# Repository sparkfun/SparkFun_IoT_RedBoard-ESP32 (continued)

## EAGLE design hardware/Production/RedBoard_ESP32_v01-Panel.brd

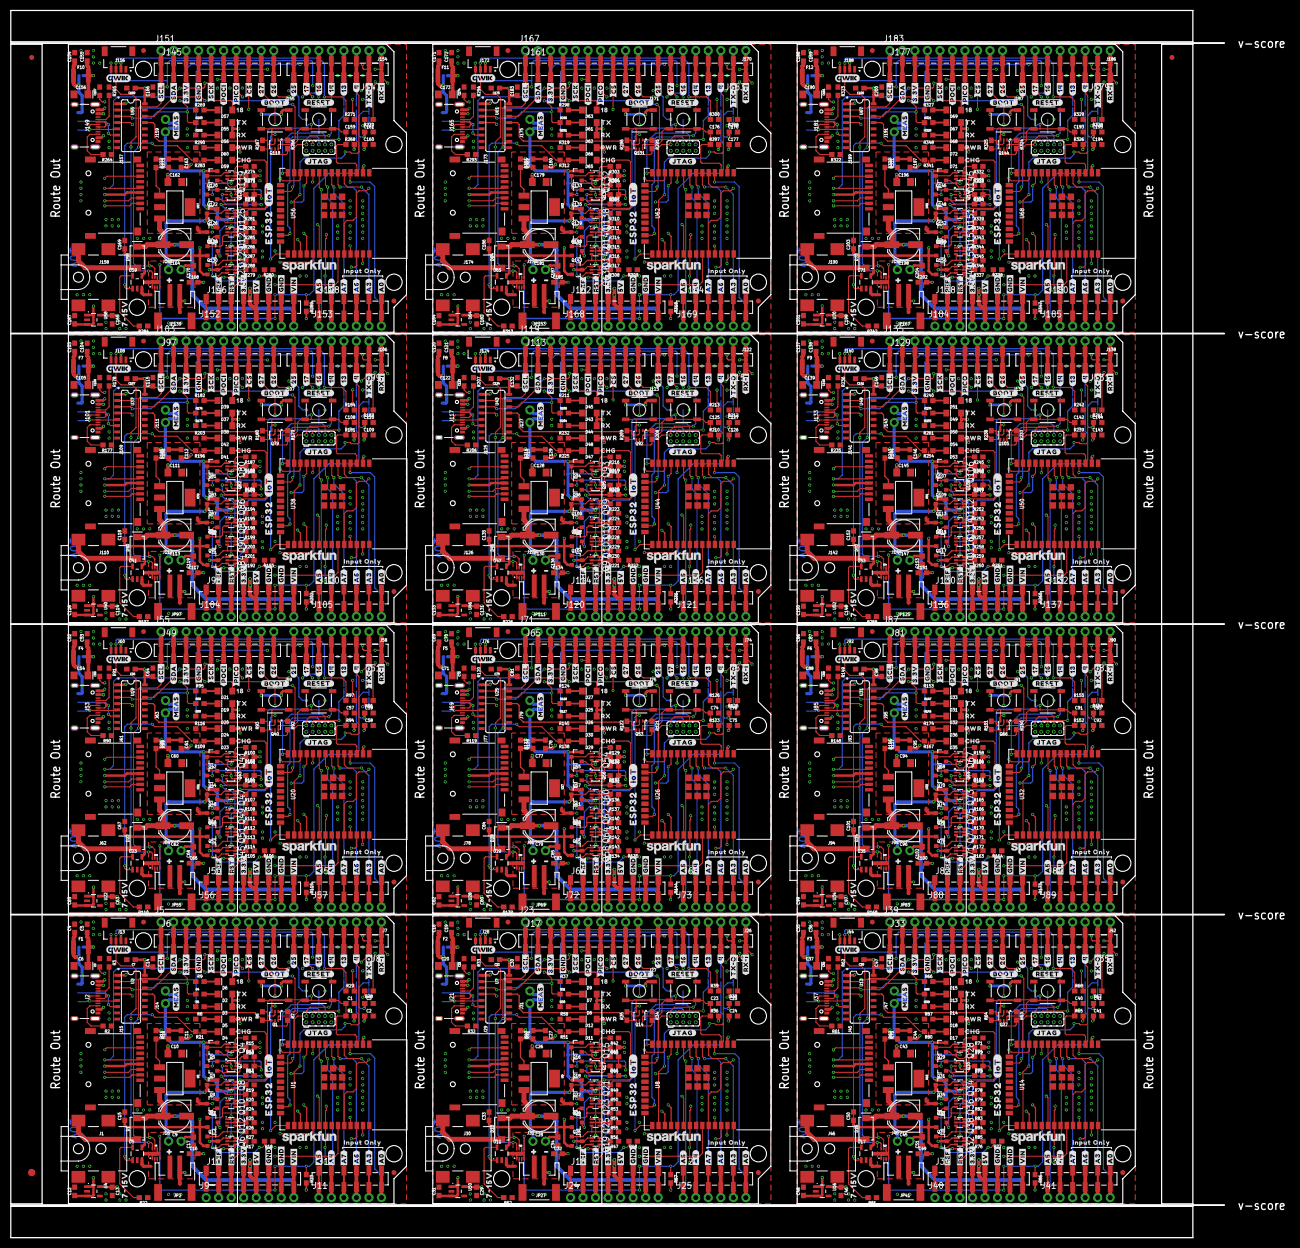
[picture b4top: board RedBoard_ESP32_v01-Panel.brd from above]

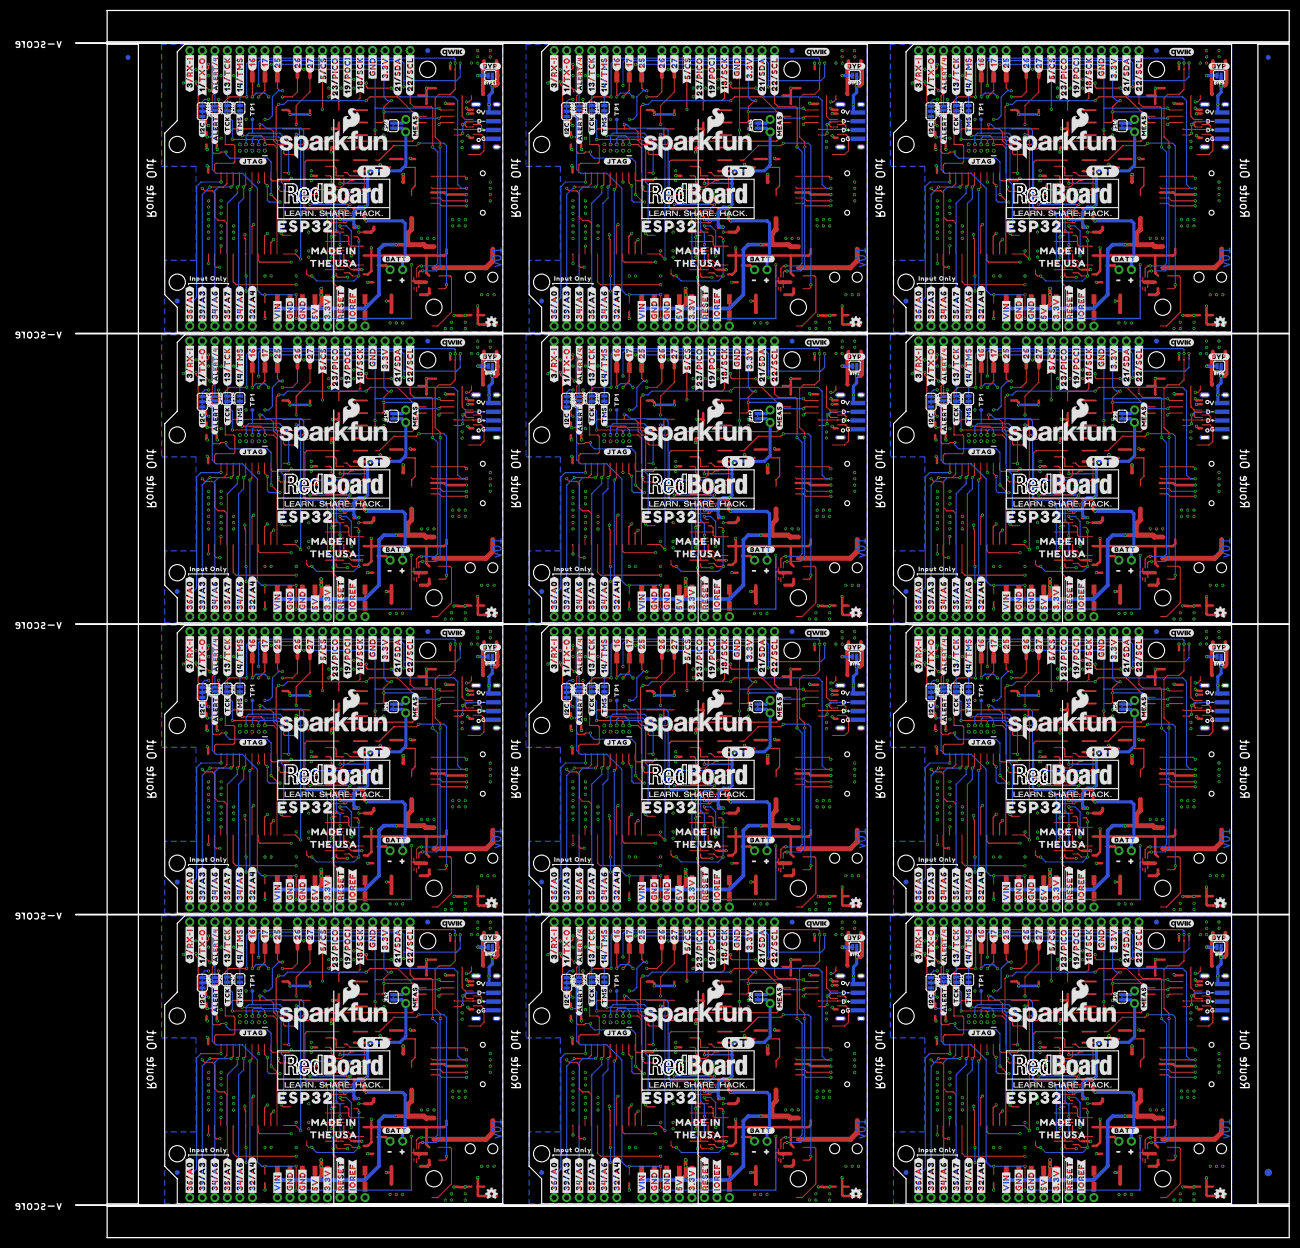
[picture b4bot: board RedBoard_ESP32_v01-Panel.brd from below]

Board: 4 copper layers, 246.1 x 248.9 mm, 2514 parts (783 on the bottom side), 876 nets.

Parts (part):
BYP, BYP1, BYP2, BYP3, BYP4, BYP5, BYP6, BYP7, BYP8, BYP9, BYP10, BYP11: JUMPER-SMT_2_NO_SILK; SMT-JUMPER_2_NO_SILK
C1, C2, C4, C5, C7, C11, C12, C13, C17, C18, C19, C22, C23, C24, C27, C29, C31, C34, C35, C36, C39, C40, C41, C44, C46, C48, C51, C52, C53, C56, C57, C58, C61, C63, C65, C68, C69, C70, C73, C74, C75, C78, C80, C82, C85, C86, C87, C90, C91, C92, C95, C97, C99, C102, C103, C104, C107, C108, C109, C112, C114, C116, C119, C120, C121, C124, C125, C126, C129, C131, C133, C136, C137, C138, C141, C142, C143, C146, C148, C150, C153, C154, C155, C158, C159, C160, C163, C165, C167, C170, C171, C172, C175, C176, C177, C180, C182, C184, C187, C188, C189, C192, C193, C194, C197, C199, C201, C204: 0.1uF; 0603
C3, C14, C25, C30, C42, C47, C59, C64, C76, C81, C93, C98, C110, C115, C127, C132, C144, C149, C161, C166, C178, C183, C195, C200: 10uF; 0603
C6, C10, C20, C26, C37, C43, C54, C60, C71, C77, C88, C94, C105, C111, C122, C128, C139, C145, C156, C162, C173, C179, C190, C196: 10uF; EIA3216
C8, C21, C38, C55, C72, C89, C106, C123, C140, C157, C174, C191: 10nF; 0603
C9, C28, C45, C62, C79, C96, C113, C130, C147, C164, C181, C198: 47uF; PANASONIC_D
C15, C16, C32, C33, C49, C50, C66, C67, C83, C84, C100, C101, C117, C118, C134, C135, C151, C152, C168, C169, C185, C186, C202, C203: 4.7uF; 0603
D1, D10, D16, D22, D28, D34, D40, D46, D52, D58, D64, D70: 1A/40V/500mV; SMA-DIODE
D2, D7, D13, D19, D25, D31, D37, D43, D49, D55, D61, D67: GREEN; LED-1206-HIDDENSILK
D3, D8, D14, D20, D26, D32, D38, D44, D50, D56, D62, D68: YELLOW; LED-1206-HIDDENSILK
D4, D11, D17, D23, D29, D35, D41, D47, D53, D59, D65, D71: RED; LED-1206-HIDDENSILK
D5, D12, D18, D24, D30, D36, D42, D48, D54, D60, D66, D72: PWR; LED-1206-HIDDENSILK
D6, D9, D15, D21, D27, D33, D39, D45, D51, D57, D63, D69: BLUE; LED-1206-HIDDENSILK
E$1, E$2, E$3, E$4: FIDUCIAL-1X2
E$5, E$6: FIDUCIAL-1.5X3
F1, F2, F3, F4, F5, F6, F7, F8, F9, F10, F11, F12: 6V/2A; 1210
J1, J30, J46, J62, J78, J94, J110, J126, J142, J158, J174, J190: 5.5x2.1mm Barrel; POWER_JACK_SMD
J2, J21, J37, J53, J69, J85, J101, J117, J133, J149, J165, J181: USB C; USB-C-16P-2LAYER-PADS
J3, J22, J38, J54, J70, J86, J102, J118, J134, J150, J166, J182: USB_SOLDER_PADS; USB-SOLDER-PADS
J4, J27, J43, J59, J75, J91, J107, J123, J139, J155, J171, J187: 2X5_PTH_SILK_.05
J5, J23, J39, J55, J71, J87, J103, J119, J135, J151, J167, J183: M10NO_SILK; 1X10_NO_SILK
J6, J17, J33, J49, J65, J81, J97, J113, J129, J145, J161, J177: 1X10_SMD_COMBINED
J7, J9, J24, J26, J40, J42, J56, J58, J72, J74, J88, J90, J104, J106, J120, J122, J136, J138, J152, J154, J168, J170, J184, J186: 1X08_NO_SILK
J8, J10, J18, J19, J34, J35, J50, J51, J66, J67, J82, J83, J98, J99, J114, J115, J130, J131, J146, J147, J162, J163, J178, J179: 1X08_SMD_COMBINED
J11, J25, J41, J57, J73, J89, J105, J121, J137, J153, J169, J185: 1X06_NO_SILK
J12, J20, J36, J52, J68, J84, J100, J116, J132, J148, J164, J180: 1X06_SMD_STRAIGHT_COMBO
J13, J28, J44, J60, J76, J92, J108, J124, J140, J156, J172, J188: QWIIC_RIGHT_ANGLE; JST04_1MM_RA
J14, J16, J31, J32, J47, J48, J63, J64, J79, J80, J95, J96, J111, J112, J127, J128, J143, J144, J159, J160, J175, J176, J191, J192: 1X02_NO_SILK
J15, J29, J45, J61, J77, J93, J109, J125, J141, J157, J173, J189: MICRO-SD-PUSH-PUSH-EXT-PIN; MICROSD-EXTERNALPIN
JP1, JP7, JP8, JP9, JP19, JP20, JP21, JP22, JP33, JP34, JP35, JP36, JP47, JP48, JP49, JP50, JP61, JP62, JP63, JP64, JP75, JP76, JP77, JP78, JP89, JP90, JP91, JP92, JP103, JP104, JP105, JP106, JP117, JP118, JP119, JP120, JP131, JP132, JP133, JP134, JP145, JP146, JP147, JP148, JP159, JP160, JP161, JP162: FIDUCIAL1X2; FIDUCIAL-1X2
JP2, JP27, JP41, JP55, JP69, JP83, JP97, JP111, JP125, JP139, JP153, JP167: LiPo; JST-2-SMD
JP3, JP4, JP5, JP6, JP15, JP16, JP17, JP18, JP29, JP30, JP31, JP32, JP43, JP44, JP45, JP46, JP57, JP58, JP59, JP60, JP71, JP72, JP73, JP74, JP85, JP86, JP87, JP88, JP99, JP100, JP101, JP102, JP113, JP114, JP115, JP116, JP127, JP128, JP129, JP130, JP141, JP142, JP143, JP144, JP155, JP156, JP157, JP158: STAND-OFF
JP10, JP13, JP14, JP25, JP26, JP28, JP39, JP40, JP42, JP53, JP54, JP56, JP67, JP68, JP70, JP81, JP82, JP84, JP95, JP96, JP98, JP109, JP110, JP112, JP123, JP124, JP126, JP137, JP138, JP140, JP151, JP152, JP154, JP165, JP166, JP168: JUMPER-SMT_2_NC_TRACE_SILK; SMT-JUMPER_2_NC_TRACE_SILK
JP11, JP23, JP37, JP51, JP65, JP79, JP93, JP107, JP121, JP135, JP149, JP163: JUMPER-SMT_3_2-NC_TRACE_SILK; SMT-JUMPER_3_2-NC_TRACE_SILK
JP12, JP24, JP38, JP52, JP66, JP80, JP94, JP108, JP122, JP136, JP150, JP164: JUMPER-SMT_2_NO_SILK; SMT-JUMPER_2_NO_SILK
LOGO1, LOGO5, LOGO11, LOGO16, LOGO21, LOGO26, LOGO31, LOGO36, LOGO41, LOGO46, LOGO51, LOGO56: SFE_LOGO_NAME.1_INCH; SFE_LOGO_NAME_.1
LOGO2, LOGO4, LOGO7, LOGO9, LOGO12, LOGO14, LOGO17, LOGO19, LOGO22, LOGO24, LOGO27, LOGO29, LOGO32, LOGO34, LOGO37, LOGO39, LOGO42, LOGO44, LOGO47, LOGO49, LOGO52, LOGO54, LOGO57, LOGO59: QWIIC_LOGO_5MM; QWIIC_5MM
LOGO3, LOGO8, LOGO13, LOGO18, LOGO23, LOGO28, LOGO33, LOGO38, LOGO43, LOGO48, LOGO53, LOGO58: OSHW-LOGOMINI; OSHW-LOGO-MINI
LOGO6, LOGO10, LOGO15, LOGO20, LOGO25, LOGO30, LOGO35, LOGO40, LOGO45, LOGO50, LOGO55, LOGO60: SFE_LOGO_NAME_FLAME.2_INCH; SFE_LOGO_NAME_FLAME_.2
Q1, Q14, Q27, Q40, Q53, Q66, Q79, Q92, Q105, Q118, Q131, Q144: MBT3904DW1T1; SC70-6
Q2, Q17, Q30, Q43, Q56, Q69, Q82, Q95, Q108, Q121, Q134, Q147: SC70-6
Q3, Q5, Q7, Q9, Q11, Q13, Q16, Q18, Q20, Q22, Q24, Q26, Q29, Q31, Q33, Q35, Q37, Q39, Q42, Q44, Q46, Q48, Q50, Q52, Q55, Q57, Q59, Q61, Q63, Q65, Q68, Q70, Q72, Q74, Q76, Q78, Q81, Q83, Q85, Q87, Q89, Q91, Q94, Q96, Q98, Q100, Q102, Q104, Q107, Q109, Q111, Q113, Q115, Q117, Q120, Q122, Q124, Q126, Q128, Q130, Q133, Q135, Q137, Q139, Q141, Q143, Q146, Q148, Q150, Q152, Q154, Q156: 20V/4.2A/52mΩ/1.4W; SOT23-3
Q4, Q6, Q8, Q10, Q12, Q15, Q19, Q21, Q23, Q25, Q28, Q32, Q34, Q36, Q38, Q41, Q45, Q47, Q49, Q51, Q54, Q58, Q60, Q62, Q64, Q67, Q71, Q73, Q75, Q77, Q80, Q84, Q86, Q88, Q90, Q93, Q97, Q99, Q101, Q103, Q106, Q110, Q112, Q114, Q116, Q119, Q123, Q125, Q127, Q129, Q132, Q136, Q138, Q140, Q142, Q145, Q149, Q151, Q153, Q155: SOT363_PHILIPS
R1, R6, R7, R8, R12, R13, R14, R15, R17, R19, R23, R24, R26, R34, R35, R36, R42, R44, R45, R46, R47, R49, R53, R55, R57, R58, R63, R64, R65, R71, R73, R74, R75, R76, R78, R82, R84, R86, R87, R92, R93, R94, R100, R102, R103, R104, R105, R107, R111, R113, R115, R116, R121, R122, R123, R129, R131, R132, R133, R134, R136, R140, R142, R144, R145, R150, R151, R152, R158, R160, R161, R162, R163, R165, R169, R171, R173, R174, R179, R180, R181, R187, R189, R190, R191, R192, R194, R198, R200, R202, R203, R208, R209, R210, R216, R218, R219, R220, R221, R223, R227, R229, R231, R232, R237, R238, R239, R245, R247, R248, R249, R250, R252, R256, R258, R260, R261, R266, R267, R268, R274, R276, R277, R278, R279, R281, R285, R287, R289, R290, R295, R296, R297, R303, R305, R306, R307, R308, R310, R314, R316, R318, R319, R324, R325, R326, R332, R334, R335, R336, R337, R339, R343, R345, R347, R348: 10k; 0603
R2, R3, R32, R33, R61, R62, R90, R91, R119, R120, R148, R149, R177, R178, R206, R207, R235, R236, R264, R265, R293, R294, R322, R323: 5.1k; 0603
R4, R5, R9, R30, R31, R37, R59, R60, R66, R88, R89, R95, R117, R118, R124, R146, R147, R153, R175, R176, R182, R204, R205, R211, R233, R234, R240, R262, R263, R269, R291, R292, R298, R320, R321, R327: 4.7k; 0603
R10, R41, R70, R99, R128, R157, R186, R215, R244, R273, R302, R331: 240; 0603
R11, R40, R69, R98, R127, R156, R185, R214, R243, R272, R301, R330: 715; 0603
R16, R18, R20, R25, R27, R43, R48, R50, R54, R56, R72, R77, R79, R83, R85, R101, R106, R108, R112, R114, R130, R135, R137, R141, R143, R159, R164, R166, R170, R172, R188, R193, R195, R199, R201, R217, R222, R224, R228, R230, R246, R251, R253, R257, R259, R275, R280, R282, R286, R288, R304, R309, R311, R315, R317, R333, R338, R340, R344, R346: 47k; 0603
R21, R51, R80, R109, R138, R167, R196, R225, R254, R283, R312, R341: 1k; 0603
R22, R52, R81, R110, R139, R168, R197, R226, R255, R284, R313, R342: 2.0k; 0603
R28, R29, R38, R39, R67, R68, R96, R97, R125, R126, R154, R155, R183, R184, R212, R213, R241, R242, R270, R271, R299, R300, R328, R329: 2.2k; 0603
S1, S3, S5, S7, S9, S11, S13, S15, S17, S19, S21, S23: Reset; TACTILE_SWITCH_SMD_5.2MM
S2, S4, S6, S8, S10, S12, S14, S16, S18, S20, S22, S24: GPIO0; TACTILE_SWITCH_SMD_5.2MM
TP1, TP2, TP3, TP4, TP5, TP6, TP7, TP8, TP9, TP10, TP11, TP12: TEST-POINT3; PAD.03X.03
U1, U8, U14, U20, U26, U32, U38, U44, U50, U56, U62, U68: ESP-WROOM-3232D-NARROW; ESP-WROOM-32D-NARROW
U2, U7, U13, U19, U25, U31, U37, U43, U49, U55, U61, U67: CH340C; SO016
U3, U9, U15, U21, U27, U33, U39, U45, U51, U57, U63, U69: LM1117; SOT223
U4, U10, U16, U22, U28, U34, U40, U46, U52, U58, U64, U70: 3.3V; SOT23-5
U5, U11, U17, U23, U29, U35, U41, U47, U53, U59, U65, U71: MCP73831; SOT23-5
U6, U12, U18, U24, U30, U36, U42, U48, U54, U60, U66, U72: MAX17048; DFN-8
U$1, U$87, U$197, U$295, U$393, U$491, U$589, U$687, U$785, U$883, U$981, U$1079: V323252
U$2, U$3, U$198, U$296, U$394, U$492, U$590, U$688, U$786, U$884, U$982, U$1080: #SCL#34
U$4, U$101, U$199, U$297, U$395, U$493, U$591, U$689, U$787, U$885, U$983, U$1081: #SDA#33
U$5, U$102, U$200, U$298, U$396, U$494, U$592, U$690, U$788, U$886, U$984, U$1082: #3#3V#33
U$6, U$103, U$201, U$299, U$397, U$495, U$593, U$691, U$789, U$887, U$985, U$1083: #GND#32
U$7, U$104, U$202, U$300, U$398, U$496, U$594, U$692, U$790, U$888, U$986, U$1084: #SCK#31
U$8, U$105, U$203, U$301, U$399, U$497, U$595, U$693, U$791, U$889, U$987, U$1085: #POCI#30
U$9, U$106, U$204, U$302, U$400, U$498, U$596, U$694, U$792, U$890, U$988, U$1086: #PICO#29
U$10, U$107, U$205, U$303, U$401, U$499, U$597, U$695, U$793, U$891, U$989, U$1087: 1836
U$11, U$108, U$206, U$304, U$402, U$500, U$598, U$696, U$794, U$892, U$990, U$1088: ##CS##28
U$12, U$109, U$207, U$305, U$403, U$501, U$599, U$697, U$795, U$893, U$991, U$1089: #27#27
U$13, U$110, U$208, U$306, U$404, U$502, U$600, U$698, U$796, U$894, U$992, U$1090: #26#26
U$14, U$111, U$209, U$307, U$405, U$503, U$601, U$699, U$797, U$895, U$993, U$1091: TX1838
U$15, U$112, U$210, U$308, U$406, U$504, U$602, U$700, U$798, U$896, U$994, U$1092: RX1839
U$16, U$113, U$211, U$309, U$407, U$505, U$603, U$701, U$799, U$897, U$995, U$1093: PWR1837
U$17, U$114, U$212, U$310, U$408, U$506, U$604, U$702, U$800, U$898, U$996, U$1094: CHG1840
U$18, U$115, U$213, U$311, U$409, U$507, U$605, U$703, U$801, U$899, U$997, U$1095: #25#18
U$19, U$116, U$214, U$312, U$410, U$508, U$606, U$704, U$802, U$900, U$998, U$1096: #17#17
U$20, U$117, U$215, U$313, U$411, U$509, U$607, U$705, U$803, U$901, U$999, U$1097: #16#15
U$21, U$118, U$216, U$314, U$412, U$510, U$608, U$706, U$804, U$902, U$1000, U$1098: #14#14
U$22, U$119, U$217, U$315, U$413, U$511, U$609, U$707, U$805, U$903, U$1001, U$1099: #13#5
U$23, U$120, U$218, U$316, U$414, U$512, U$610, U$708, U$806, U$904, U$1002, U$1100: #4#2
U$24, U$121, U$219, U$317, U$415, U$513, U$611, U$709, U$807, U$905, U$1003, U$1101: #TX#O#0
U$25, U$122, U$220, U$318, U$416, U$514, U$612, U$710, U$808, U$906, U$1004, U$1102: #RX#I#1
U$26, U$123, U$221, U$319, U$417, U$515, U$613, U$711, U$809, U$907, U$1005, U$1103: #RESET#1842
U$27, U$124, U$222, U$320, U$418, U$516, U$614, U$712, U$810, U$908, U$1006, U$1104: #BOOT#1841
U$28, U$46, U$125, U$143, U$223, U$241, U$321, U$339, U$419, U$437, U$517, U$535, U$615, U$633, U$713, U$731, U$811, U$829, U$909, U$927, U$1007, U$1025, U$1105, U$1123: #JTAG#1847
U$29, U$126, U$224, U$322, U$420, U$518, U$616, U$714, U$812, U$910, U$1008, U$1106: #A0#1843
U$30, U$127, U$225, U$323, U$421, U$519, U$617, U$715, U$813, U$911, U$1009, U$1107: #A3#1843
U$31, U$128, U$226, U$324, U$422, U$520, U$618, U$716, U$814, U$912, U$1010, U$1108: #A6#1843
U$32, U$129, U$227, U$325, U$423, U$521, U$619, U$717, U$815, U$913, U$1011, U$1109: #A7#1843
U$33, U$130, U$228, U$326, U$424, U$522, U$620, U$718, U$816, U$914, U$1012, U$1110: #A4#1843
U$34, U$131, U$229, U$327, U$425, U$523, U$621, U$719, U$817, U$915, U$1013, U$1111: #A5#1843
U$35, U$132, U$230, U$328, U$426, U$524, U$622, U$720, U$818, U$916, U$1014, U$1112: #VIN#1843
U$36, U$37, U$133, U$134, U$231, U$232, U$329, U$330, U$427, U$428, U$525, U$526, U$623, U$624, U$721, U$722, U$819, U$820, U$917, U$918, U$1015, U$1016, U$1113, U$1114: #GND#1844
U$38, U$135, U$233, U$331, U$429, U$527, U$625, U$723, U$821, U$919, U$1017, U$1115: #5V#1845
U$39, U$136, U$234, U$332, U$430, U$528, U$626, U$724, U$822, U$920, U$1018, U$1116: #3#3V#1845
U$40, U$137, U$235, U$333, U$431, U$529, U$627, U$725, U$823, U$921, U$1019, U$1117: ##RST##1845
U$41, U$138, U$236, U$334, U$432, U$530, U$628, U$726, U$824, U$922, U$1020, U$1118: #REF#1846
U$42, U$81, U$139, U$176, U$237, U$274, U$335, U$372, U$433, U$470, U$531, U$568, U$629, U$666, U$727, U$764, U$825, U$862, U$923, U$960, U$1021, U$1058, U$1119, U$1156: #MEAS#1851
U$43, U$86, U$140, U$181, U$238, U$279, U$336, U$377, U$434, U$475, U$532, U$573, U$630, U$671, U$728, U$769, U$826, U$867, U$924, U$965, U$1022, U$1063, U$1120, U$1161: #1849
U$44, U$88, U$141, U$182, U$239, U$280, U$337, U$378, U$435, U$476, U$533, U$574, U$631, U$672, U$729, U$770, U$827, U$868, U$925, U$966, U$1023, U$1064, U$1121, U$1162: #1850
U$45, U$142, U$240, U$338, U$436, U$534, U$632, U$730, U$828, U$926, U$1024, U$1122: #BATT#1848
U$47, U$194, U$292, U$390, U$488, U$586, U$684, U$782, U$880, U$978, U$1076, U$1174: #IOT#132321874
U$48, U$144, U$242, U$340, U$438, U$536, U$634, U$732, U$830, U$928, U$1026, U$1124: ESP321855
U$49, U$145, U$243, U$341, U$439, U$537, U$635, U$733, U$831, U$929, U$1027, U$1125: 7#15V32321861
U$50, U$146, U$244, U$342, U$440, U$538, U$636, U$734, U$832, U$930, U$1028, U$1126: #39#A3#321862
U$51, U$147, U$245, U$343, U$441, U$539, U$637, U$735, U$833, U$931, U$1029, U$1127: #36#A0#321862
U$52, U$148, U$246, U$344, U$442, U$540, U$638, U$736, U$834, U$932, U$1030, U$1128: #34#A6#32321865
U$53, U$149, U$247, U$345, U$443, U$541, U$639, U$737, U$835, U$933, U$1031, U$1129: #35#A7#321862
U$54, U$150, U$248, U$346, U$444, U$542, U$640, U$738, U$836, U$934, U$1032, U$1130: #32#A4#32321865
U$55, U$151, U$249, U$347, U$445, U$543, U$641, U$739, U$837, U$935, U$1033, U$1131: #34#A6#321862
U$56, U$152, U$250, U$348, U$446, U$544, U$642, U$740, U$838, U$936, U$1034, U$1132: #VIN#321862
U$57, U$60, U$153, U$156, U$251, U$254, U$349, U$352, U$447, U$450, U$545, U$548, U$643, U$646, U$741, U$744, U$839, U$842, U$937, U$940, U$1035, U$1038, U$1133, U$1136: #GND#321863
U$58, U$154, U$252, U$350, U$448, U$546, U$644, U$742, U$840, U$938, U$1036, U$1134: #5V#321864
U$59, U$155, U$253, U$351, U$449, U$547, U$645, U$743, U$841, U$939, U$1037, U$1135: #3#3V#321864
U$61, U$157, U$255, U$353, U$451, U$549, U$647, U$745, U$843, U$941, U$1039, U$1137: ##RESET##321864
U$62, U$158, U$256, U$354, U$452, U$550, U$648, U$746, U$844, U$942, U$1040, U$1138: #IOREF#321865
U$63, U$159, U$257, U$355, U$453, U$551, U$649, U$747, U$845, U$943, U$1041, U$1139: #3#RX#I#32321869
U$64, U$160, U$258, U$356, U$454, U$552, U$650, U$748, U$846, U$944, U$1042, U$1140: #1#TX#O#32321869
U$65, U$189, U$287, U$385, U$483, U$581, U$679, U$777, U$875, U$973, U$1071, U$1169: ##ALERT##4#321866
U$66, U$161, U$259, U$357, U$455, U$553, U$651, U$749, U$847, U$945, U$1043, U$1141: #13#TCK#32321869
U$67, U$162, U$260, U$358, U$456, U$554, U$652, U$750, U$848, U$946, U$1044, U$1142: #14#TMS#32321869
U$68, U$163, U$261, U$359, U$457, U$555, U$653, U$751, U$849, U$947, U$1045, U$1143: #16#32321869
U$69, U$164, U$262, U$360, U$458, U$556, U$654, U$752, U$850, U$948, U$1046, U$1144: #17#32321869
U$70, U$165, U$263, U$361, U$459, U$557, U$655, U$753, U$851, U$949, U$1047, U$1145: #25#32321869
U$71, U$166, U$264, U$362, U$460, U$558, U$656, U$754, U$852, U$950, U$1048, U$1146: #26#32321869
U$72, U$167, U$265, U$363, U$461, U$559, U$657, U$755, U$853, U$951, U$1049, U$1147: #5##CS##32321869
U$73, U$168, U$266, U$364, U$462, U$560, U$658, U$756, U$854, U$952, U$1050, U$1148: #23#PICO#321866
U$74, U$169, U$267, U$365, U$463, U$561, U$659, U$757, U$855, U$953, U$1051, U$1149: #19#POCI#321866
U$75, U$170, U$268, U$366, U$464, U$562, U$660, U$758, U$856, U$954, U$1052, U$1150: #18#SCK#32321869
U$76, U$171, U$269, U$367, U$465, U$563, U$661, U$759, U$857, U$955, U$1053, U$1151: #21#SDA#32321869
U$77, U$172, U$270, U$368, U$466, U$564, U$662, U$760, U$858, U$956, U$1054, U$1152: #22#SCL#32321869
U$78, U$173, U$271, U$369, U$467, U$565, U$663, U$761, U$859, U$957, U$1055, U$1153: #27#32321869
U$79, U$174, U$272, U$370, U$468, U$566, U$664, U$762, U$860, U$958, U$1056, U$1154: #GND#321866
U$80, U$175, U$273, U$371, U$469, U$567, U$665, U$763, U$861, U$959, U$1057, U$1155: #3#3V#321866
U$82, U$177, U$275, U$373, U$471, U$569, U$667, U$765, U$863, U$961, U$1059, U$1157: #BYP#35
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
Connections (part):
3.3V: C2.1, C3.1, C7.1, C13.1, C14.1, D2.A, D3.A, D5.A, J5.3, J6.3A, J6.3B, J9.2, J9.4, J10.2, J10.4, J13.2, J15.4, JP11.2, R1.2, R23.2, U1.2, U2.16, U4.5
3.3V1: C22.1, C24.1, C25.1, C29.1, C30.1, D7.A, D8.A, D12.A, J17.3A, J17.3B, J18.2, J18.4, J23.3, J24.2, J24.4, J28.2, J29.4, JP23.2, R36.2, R57.2, U7.16, U8.2, U10.5
3.3V2: C39.1, C41.1, C42.1, C46.1, C47.1, D13.A, D14.A, D18.A, J33.3A, J33.3B, J34.2, J34.4, J39.3, J40.2, J40.4, J44.2, J45.4, JP37.2, R65.2, R86.2, U13.16, U14.2, U16.5
3.3V3: C56.1, C58.1, C59.1, C63.1, C64.1, D19.A, D20.A, D24.A, J49.3A, J49.3B, J50.2, J50.4, J55.3, J56.2, J56.4, J60.2, J61.4, JP51.2, R94.2, R115.2, U19.16, U20.2, U22.5
3.3V4: C73.1, C75.1, C76.1, C80.1, C81.1, D25.A, D26.A, D30.A, J65.3A, J65.3B, J66.2, J66.4, J71.3, J72.2, J72.4, J76.2, J77.4, JP65.2, R123.2, R144.2, U25.16, U26.2, U28.5
3.3V5: C90.1, C92.1, C93.1, C97.1, C98.1, D31.A, D32.A, D36.A, J81.3A, J81.3B, J82.2, J82.4, J87.3, J88.2, J88.4, J92.2, J93.4, JP79.2, R152.2, R173.2, U31.16, U32.2, U34.5
3.3V6: C107.1, C109.1, C110.1, C114.1, C115.1, D37.A, D38.A, D42.A, J97.3A, J97.3B, J98.2, J98.4, J103.3, J104.2, J104.4, J108.2, J109.4, JP93.2, R181.2, R202.2, U37.16, U38.2, U40.5
3.3V7: C124.1, C126.1, C127.1, C131.1, C132.1, D43.A, D44.A, D48.A, J113.3A, J113.3B, J114.2, J114.4, J119.3, J120.2, J120.4, J124.2, J125.4, JP107.2, R210.2, R231.2, U43.16, U44.2, U46.5
3.3V8: C141.1, C143.1, C144.1, C148.1, C149.1, D49.A, D50.A, D54.A, J129.3A, J129.3B, J130.2, J130.4, J135.3, J136.2, J136.4, J140.2, J141.4, JP121.2, R239.2, R260.2, U49.16, U50.2, U52.5
3.3V9: C158.1, C160.1, C161.1, C165.1, C166.1, D55.A, D56.A, D60.A, J145.3A, J145.3B, J146.2, J146.4, J151.3, J152.2, J152.4, J156.2, J157.4, JP135.2, R268.2, R289.2, U55.16, U56.2, U58.5
3.3V10: C175.1, C177.1, C178.1, C182.1, C183.1, D61.A, D62.A, D66.A, J161.3A, J161.3B, J162.2, J162.4, J167.3, J168.2, J168.4, J172.2, J173.4, JP149.2, R297.2, R318.2, U61.16, U62.2, U64.5
3.3V11: C192.1, C194.1, C195.1, C199.1, C200.1, D67.A, D68.A, D72.A, J177.3A, J177.3B, J178.2, J178.4, J183.3, J184.2, J184.4, J188.2, J189.4, JP163.2, R326.2, R347.2, U67.16, U68.2, U70.5
5V: C12.1, J9.5, J10.5, J14.2, JP10.2, U4.1, U4.3
5V1: C31.1, J18.5, J24.5, J31.2, JP28.2, U10.1, U10.3
5V2: C48.1, J34.5, J40.5, J47.2, JP42.2, U16.1, U16.3
5V3: C65.1, J50.5, J56.5, J63.2, JP56.2, U22.1, U22.3
5V4: C82.1, J66.5, J72.5, J79.2, JP70.2, U28.1, U28.3
5V5: C99.1, J82.5, J88.5, J95.2, JP84.2, U34.1, U34.3
5V6: C116.1, J98.5, J104.5, J111.2, JP98.2, U40.1, U40.3
5V7: C133.1, J114.5, J120.5, J127.2, JP112.2, U46.1, U46.3
5V8: C150.1, J130.5, J136.5, J143.2, JP126.2, U52.1, U52.3
5V9: C167.1, J146.5, J152.5, J159.2, JP140.2, U58.1, U58.3
5V10: C184.1, J162.5, J168.5, J175.2, JP154.2, U64.1, U64.3
5V11: C201.1, J178.5, J184.5, J191.2, JP168.2, U70.1, U70.3
5V_CHG: C15.1, D4.A, Q10.4, Q11.2, Q12.4, Q13.2, U5.4
5V_CHG1: C33.1, D11.A, Q23.4, Q24.2, Q25.4, Q26.2, U11.4
5V_CHG2: C50.1, D17.A, Q36.4, Q37.2, Q38.4, Q39.2, U17.4
5V_CHG3: C67.1, D23.A, Q49.4, Q50.2, Q51.4, Q52.2, U23.4
5V_CHG4: C84.1, D29.A, Q62.4, Q63.2, Q64.4, Q65.2, U29.4
5V_CHG5: C101.1, D35.A, Q75.4, Q76.2, Q77.4, Q78.2, U35.4
5V_CHG6: C118.1, D41.A, Q88.4, Q89.2, Q90.4, Q91.2, U41.4
5V_CHG7: C135.1, D47.A, Q101.4, Q102.2, Q103.4, Q104.2, U47.4
5V_CHG8: C152.1, D53.A, Q114.4, Q115.2, Q116.4, Q117.2, U53.4
5V_CHG9: C169.1, D59.A, Q127.4, Q128.2, Q129.4, Q130.2, U59.4
5V_CHG10: C186.1, D65.A, Q140.4, Q141.2, Q142.4, Q143.2, U65.4
5V_CHG11: C203.1, D71.A, Q153.4, Q154.2, Q155.4, Q156.2, U71.4
5V_EXT: C10.+, C11.1, Q6.1, Q7.3, Q12.1, Q13.3, R10.2, R12.1, U3.2, U3.4
5V_EXT1: C26.+, C27.1, Q19.1, Q20.3, Q25.1, Q26.3, R41.2, R46.1, U9.2, U9.4
5V_EXT2: C43.+, C44.1, Q32.1, Q33.3, Q38.1, Q39.3, R70.2, R75.1, U15.2, U15.4
5V_EXT3: C60.+, C61.1, Q45.1, Q46.3, Q51.1, Q52.3, R99.2, R104.1, U21.2, U21.4
5V_EXT4: C77.+, C78.1, Q58.1, Q59.3, Q64.1, Q65.3, R128.2, R133.1, U27.2, U27.4
5V_EXT5: C94.+, C95.1, Q71.1, Q72.3, Q77.1, Q78.3, R157.2, R162.1, U33.2, U33.4
5V_EXT6: C111.+, C112.1, Q84.1, Q85.3, Q90.1, Q91.3, R186.2, R191.1, U39.2, U39.4
5V_EXT7: C128.+, C129.1, Q97.1, Q98.3, Q103.1, Q104.3, R215.2, R220.1, U45.2, U45.4
5V_EXT8: C145.+, C146.1, Q110.1, Q111.3, Q116.1, Q117.3, R244.2, R249.1, U51.2, U51.4
5V_EXT9: C162.+, C163.1, Q123.1, Q124.3, Q129.1, Q130.3, R273.2, R278.1, U57.2, U57.4
5V_EXT10: C179.+, C180.1, Q136.1, Q137.3, Q142.1, Q143.3, R302.2, R307.1, U63.2, U63.4
5V_EXT11: C196.+, C197.1, Q149.1, Q150.3, Q155.1, Q156.3, R331.2, R336.1, U69.2, U69.4
5V_MEAS: J14.1, JP10.1, Q4.4, Q5.2, Q6.4, Q7.2, Q8.4, Q9.2
5V_MEAS1: J31.1, JP28.1, Q15.4, Q16.2, Q19.4, Q20.2, Q21.4, Q22.2
5V_MEAS2: J47.1, JP42.1, Q28.4, Q29.2, Q32.4, Q33.2, Q34.4, Q35.2
5V_MEAS3: J63.1, JP56.1, Q41.4, Q42.2, Q45.4, Q46.2, Q47.4, Q48.2
5V_MEAS4: J79.1, JP70.1, Q54.4, Q55.2, Q58.4, Q59.2, Q60.4, Q61.2
5V_MEAS5: J95.1, JP84.1, Q67.4, Q68.2, Q71.4, Q72.2, Q73.4, Q74.2
5V_MEAS6: J111.1, JP98.1, Q80.4, Q81.2, Q84.4, Q85.2, Q86.4, Q87.2
5V_MEAS7: J127.1, JP112.1, Q93.4, Q94.2, Q97.4, Q98.2, Q99.4, Q100.2
5V_MEAS8: J143.1, JP126.1, Q106.4, Q107.2, Q110.4, Q111.2, Q112.4, Q113.2
5V_MEAS9: J159.1, JP140.1, Q119.4, Q120.2, Q123.4, Q124.2, Q125.4, Q126.2
5V_MEAS10: J175.1, JP154.1, Q132.4, Q133.2, Q136.4, Q137.2, Q138.4, Q139.2
5V_MEAS11: J191.1, JP168.1, Q145.4, Q146.2, Q149.4, Q150.2, Q151.4, Q152.2
!DTR!: Q1.4, R6.1, U2.13
!DTR!1: Q14.4, R35.1, U7.13
!DTR!2: Q27.4, R64.1, U13.13
!DTR!3: Q40.4, R93.1, U19.13
!DTR!4: Q53.4, R122.1, U25.13
!DTR!5: Q66.4, R151.1, U31.13
!DTR!6: Q79.4, R180.1, U37.13
!DTR!7: Q92.4, R209.1, U43.13
!DTR!8: Q105.4, R238.1, U49.13
!DTR!9: Q118.4, R267.1, U55.13
!DTR!10: Q131.4, R296.1, U61.13
!DTR!11: Q144.4, R325.1, U67.13
!GAUGE_ALERT!: JP12.1, R23.1, U6.5
!GAUGE_ALERT!1: JP24.1, R57.1, U12.5
!GAUGE_ALERT!2: JP38.1, R86.1, U18.5
!GAUGE_ALERT!3: JP52.1, R115.1, U24.5
!GAUGE_ALERT!4: JP66.1, R144.1, U30.5
!GAUGE_ALERT!5: JP80.1, R173.1, U36.5
!GAUGE_ALERT!6: JP94.1, R202.1, U42.5
!GAUGE_ALERT!7: JP108.1, R231.1, U48.5
!GAUGE_ALERT!8: JP122.1, R260.1, U54.5
!GAUGE_ALERT!9: JP136.1, R289.1, U60.5
!GAUGE_ALERT!10: JP150.1, R318.1, U66.5
!GAUGE_ALERT!11: JP164.1, R347.1, U72.5
!RTS!: Q1.1, R7.1, U2.14
!RTS!1: Q14.1, R34.1, U7.14
!RTS!2: Q27.1, R63.1, U13.14
!RTS!3: Q40.1, R92.1, U19.14
!RTS!4: Q53.1, R121.1, U25.14
!RTS!5: Q66.1, R150.1, U31.14
!RTS!6: Q79.1, R179.1, U37.14
!RTS!7: Q92.1, R208.1, U43.14
!RTS!8: Q105.1, R237.1, U49.14
!RTS!9: Q118.1, R266.1, U55.14
!RTS!10: Q131.1, R295.1, U61.14
!RTS!11: Q144.1, R324.1, U67.14
CC1: J2.A5, R3.2
CC2: J2.B5, R2.2
CC3: J21.B5, R32.2
CC4: J21.A5, R33.2
CC5: J37.B5, R61.2
CC6: J37.A5, R62.2
CC7: J53.B5, R90.2
CC8: J53.A5, R91.2
CC9: J69.B5, R119.2
CC10: J69.A5, R120.2
CC11: J85.B5, R148.2
CC12: J85.A5, R149.2
CC13: J101.B5, R177.2
CC14: J101.A5, R178.2
CC15: J117.B5, R206.2
CC16: J117.A5, R207.2
CC17: J133.B5, R235.2
CC18: J133.A5, R236.2
CC19: J149.B5, R264.2
CC20: J149.A5, R265.2
CC21: J165.B5, R293.2
CC22: J165.A5, R294.2
CC23: J181.B5, R322.2
CC24: J181.A5, R323.2
D+: J2.A6, J2.B6, J3.D+, U2.5
D+1: J21.A6, J21.B6, J22.D+, U7.5
D+2: J37.A6, J37.B6, J38.D+, U13.5
D+3: J53.A6, J53.B6, J54.D+, U19.5
D+4: J69.A6, J69.B6, J70.D+, U25.5
D+5: J85.A6, J85.B6, J86.D+, U31.5
D+6: J101.A6, J101.B6, J102.D+, U37.5
D+7: J117.A6, J117.B6, J118.D+, U43.5
D+8: J133.A6, J133.B6, J134.D+, U49.5
D+9: J149.A6, J149.B6, J150.D+, U55.5
D+10: J165.A6, J165.B6, J166.D+, U61.5
D+11: J181.A6, J181.B6, J182.D+, U67.5
D-: J2.A7, J2.B7, J3.D-, U2.6
D-1: J21.A7, J21.B7, J22.D-, U7.6
D-2: J37.A7, J37.B7, J38.D-, U13.6
D-3: J53.A7, J53.B7, J54.D-, U19.6
D-4: J69.A7, J69.B7, J70.D-, U25.6
D-5: J85.A7, J85.B7, J86.D-, U31.6
D-6: J101.A7, J101.B7, J102.D-, U37.6
D-7: J117.A7, J117.B7, J118.D-, U43.6
D-8: J133.A7, J133.B7, J134.D-, U49.6
D-9: J149.A7, J149.B7, J150.D-, U55.6
D-10: J165.A7, J165.B7, J166.D-, U61.6
D-11: J181.A7, J181.B7, J182.D-, U67.6
ESP32_0: Q1.3, S2.3, S2.4, U1.25
ESP32_1: Q14.3, S4.3, S4.4, U8.25
ESP32_2: Q27.3, S6.3, S6.4, U14.25
ESP32_3: Q40.3, S8.3, S8.4, U20.25
ESP32_4: Q53.3, S10.3, S10.4, U26.25
ESP32_5: Q66.3, S12.3, S12.4, U32.25
ESP32_6: Q79.3, S14.3, S14.4, U38.25
ESP32_7: Q92.3, S16.3, S16.4, U44.25
ESP32_8: Q105.3, S18.3, S18.4, U50.25
ESP32_9: Q118.3, S20.3, S20.4, U56.25
ESP32_10: Q131.3, S22.3, S22.4, U62.25
ESP32_11: Q144.3, S24.3, S24.4, U68.25
ESP32_ADC0: J11.6, J12.6, U1.4
ESP32_ADC1: J20.6, J25.6, U8.4
ESP32_ADC2: J20.5, J25.5, U8.5
ESP32_ADC3: J11.5, J12.5, U1.5
ESP32_ADC4: J11.2, J12.2, U1.8
ESP32_ADC5: J11.1, J12.1, U1.9
ESP32_ADC6: J11.4, J12.4, U1.6
ESP32_ADC7: J11.3, J12.3, U1.7
ESP32_ADC8: J20.4, J25.4, U8.6
ESP32_ADC9: J20.3, J25.3, U8.7
ESP32_ADC10: J20.1, J25.1, U8.9
ESP32_ADC11: J20.2, J25.2, U8.8
ESP32_ADC12: J36.6, J41.6, U14.4
ESP32_ADC13: J36.5, J41.5, U14.5
ESP32_ADC14: J36.4, J41.4, U14.6
ESP32_ADC15: J36.3, J41.3, U14.7
ESP32_ADC16: J36.1, J41.1, U14.9
ESP32_ADC17: J36.2, J41.2, U14.8
ESP32_ADC18: J52.6, J57.6, U20.4
ESP32_ADC19: J52.5, J57.5, U20.5
ESP32_ADC20: J52.4, J57.4, U20.6
ESP32_ADC21: J52.3, J57.3, U20.7
ESP32_ADC22: J52.1, J57.1, U20.9
ESP32_ADC23: J52.2, J57.2, U20.8
ESP32_ADC24: J68.6, J73.6, U26.4
ESP32_ADC25: J68.5, J73.5, U26.5
ESP32_ADC26: J68.4, J73.4, U26.6
ESP32_ADC27: J68.3, J73.3, U26.7
ESP32_ADC28: J68.1, J73.1, U26.9
ESP32_ADC29: J68.2, J73.2, U26.8
ESP32_ADC30: J84.6, J89.6, U32.4
ESP32_ADC31: J84.5, J89.5, U32.5
ESP32_ADC32: J84.4, J89.4, U32.6
ESP32_ADC33: J84.3, J89.3, U32.7
ESP32_ADC34: J84.1, J89.1, U32.9
ESP32_ADC35: J84.2, J89.2, U32.8
ESP32_ADC36: J100.6, J105.6, U38.4
ESP32_ADC37: J100.5, J105.5, U38.5
ESP32_ADC38: J100.4, J105.4, U38.6
ESP32_ADC39: J100.3, J105.3, U38.7
ESP32_ADC40: J100.1, J105.1, U38.9
ESP32_ADC41: J100.2, J105.2, U38.8
ESP32_ADC42: J116.6, J121.6, U44.4
ESP32_ADC43: J116.5, J121.5, U44.5
ESP32_ADC44: J116.4, J121.4, U44.6
ESP32_ADC45: J116.3, J121.3, U44.7
ESP32_ADC46: J116.1, J121.1, U44.9
ESP32_ADC47: J116.2, J121.2, U44.8
ESP32_ADC48: J132.6, J137.6, U50.4
ESP32_ADC49: J132.5, J137.5, U50.5
ESP32_ADC50: J132.4, J137.4, U50.6
ESP32_ADC51: J132.3, J137.3, U50.7
ESP32_ADC52: J132.1, J137.1, U50.9
ESP32_ADC53: J132.2, J137.2, U50.8
ESP32_ADC54: J148.6, J153.6, U56.4
ESP32_ADC55: J148.5, J153.5, U56.5
ESP32_ADC56: J148.4, J153.4, U56.6
ESP32_ADC57: J148.3, J153.3, U56.7
ESP32_ADC58: J148.1, J153.1, U56.9
ESP32_ADC59: J148.2, J153.2, U56.8
ESP32_ADC60: J164.6, J169.6, U62.4
ESP32_ADC61: J164.5, J169.5, U62.5
ESP32_ADC62: J164.4, J169.4, U62.6
ESP32_ADC63: J164.3, J169.3, U62.7
ESP32_ADC64: J164.1, J169.1, U62.9
ESP32_ADC65: J164.2, J169.2, U62.8
ESP32_ADC66: J180.6, J185.6, U68.4
ESP32_ADC67: J180.5, J185.5, U68.5
ESP32_ADC68: J180.4, J185.4, U68.6
ESP32_ADC69: J180.3, J185.3, U68.7
ESP32_ADC70: J180.1, J185.1, U68.9
ESP32_ADC71: J180.2, J185.2, U68.8
ESP32_EN: C1.1, J9.3, J10.3, Q1.6, R1.1, S1.3, S1.4, U1.3
ESP32_EN1: C23.1, J18.3, J24.3, Q14.6, R36.1, S3.3, S3.4, U8.3
ESP32_EN2: C40.1, J34.3, J40.3, Q27.6, R65.1, S5.3, S5.4, U14.3
ESP32_EN3: C57.1, J50.3, J56.3, Q40.6, R94.1, S7.3, S7.4, U20.3
ESP32_EN4: C74.1, J66.3, J72.3, Q53.6, R123.1, S9.3, S9.4, U26.3
ESP32_EN5: C91.1, J82.3, J88.3, Q66.6, R152.1, S11.3, S11.4, U32.3
ESP32_EN6: C108.1, J98.3, J104.3, Q79.6, R181.1, S13.3, S13.4, U38.3
ESP32_EN7: C125.1, J114.3, J120.3, Q92.6, R210.1, S15.3, S15.4, U44.3
ESP32_EN8: C142.1, J130.3, J136.3, Q105.6, R239.1, S17.3, S17.4, U50.3
ESP32_EN9: C159.1, J146.3, J152.3, Q118.6, R268.1, S19.3, S19.4, U56.3
ESP32_EN10: C176.1, J162.3, J168.3, Q131.6, R297.1, S21.3, S21.4, U62.3
ESP32_EN11: C193.1, J178.3, J184.3, Q144.6, R326.1, S23.3, S23.4, U68.3
ESP32_GPIO3: J19.3, J26.3, JP24.2, U8.26
ESP32_GPIO4: J7.3, J8.3, JP12.2, U1.26
ESP32_GPIO5: J19.7, J26.7, U8.28
ESP32_GPIO5_!CS!: J5.8, J6.8A, J6.8B, J15.2, U1.29
ESP32_GPIO5_!CS!1: J17.8A, J17.8B, J23.8, J29.2, U8.29
ESP32_GPIO5_!CS!2: J33.8A, J33.8B, J39.8, J45.2, U14.29
ESP32_GPIO5_!CS!3: J49.8A, J49.8B, J55.8, J61.2, U20.29
ESP32_GPIO5_!CS!4: J65.8A, J65.8B, J71.8, J77.2, U26.29
ESP32_GPIO5_!CS!5: J81.8A, J81.8B, J87.8, J93.2, U32.29
ESP32_GPIO5_!CS!6: J97.8A, J97.8B, J103.8, J109.2, U38.29
ESP32_GPIO5_!CS!7: J113.8A, J113.8B, J119.8, J125.2, U44.29
ESP32_GPIO5_!CS!8: J129.8A, J129.8B, J135.8, J141.2, U50.29
ESP32_GPIO5_!CS!9: J145.8A, J145.8B, J151.8, J157.2, U56.29
ESP32_GPIO5_!CS!10: J161.8A, J161.8B, J167.8, J173.2, U62.29
ESP32_GPIO5_!CS!11: J177.8A, J177.8B, J183.8, J189.2, U68.29
ESP32_GPIO6: J19.8, J26.8, U8.10
ESP32_GPIO7: J17.10A, J17.10B, J23.10, U8.11
ESP32_GPIO8: J17.9A, J17.9B, J23.9, U8.12
ESP32_GPIO9: J19.6, J26.6, U8.27
ESP32_GPIO11: J35.3, J42.3, JP38.2, U14.26
ESP32_GPIO12: J35.7, J42.7, U14.28
ESP32_GPIO12_TDI: J4.8, TP1.1, U1.14
ESP32_GPIO12_TDI1: J27.8, TP2.1, U8.14
ESP32_GPIO12_TDI2: J43.8, TP3.1, U14.14
ESP32_GPIO12_TDI3: J59.8, TP4.1, U20.14
ESP32_GPIO12_TDI4: J75.8, TP5.1, U26.14
ESP32_GPIO12_TDI5: J91.8, TP6.1, U32.14
ESP32_GPIO12_TDI6: J107.8, TP7.1, U38.14
ESP32_GPIO12_TDI7: J123.8, TP8.1, U44.14
ESP32_GPIO12_TDI8: J139.8, TP9.1, U50.14
ESP32_GPIO12_TDI9: J155.8, TP10.1, U56.14
ESP32_GPIO12_TDI10: J171.8, TP11.1, U62.14
ESP32_GPIO12_TDI11: J187.8, TP12.1, U68.14
ESP32_GPIO13: J35.8, J42.8, U14.10
ESP32_GPIO13_HDR: J7.4, J8.4, JP13.2
ESP32_GPIO13_HDR1: J19.4, J26.4, JP25.2
ESP32_GPIO13_HDR2: J35.4, J42.4, JP39.2
ESP32_GPIO13_HDR3: J51.4, J58.4, JP53.2
ESP32_GPIO13_HDR4: J67.4, J74.4, JP67.2
ESP32_GPIO13_HDR5: J83.4, J90.4, JP81.2
ESP32_GPIO13_HDR6: J99.4, J106.4, JP95.2
ESP32_GPIO13_HDR7: J115.4, J122.4, JP109.2
ESP32_GPIO13_HDR8: J131.4, J138.4, JP123.2
ESP32_GPIO13_HDR9: J147.4, J154.4, JP137.2
ESP32_GPIO13_HDR10: J163.4, J170.4, JP151.2
ESP32_GPIO13_HDR11: J179.4, J186.4, JP165.2
ESP32_GPIO13_TCK: J4.4, JP13.1, U1.16
ESP32_GPIO13_TCK1: J27.4, JP25.1, U8.16
ESP32_GPIO13_TCK2: J43.4, JP39.1, U14.16
ESP32_GPIO13_TCK3: J59.4, JP53.1, U20.16
ESP32_GPIO13_TCK4: J75.4, JP67.1, U26.16
ESP32_GPIO13_TCK5: J91.4, JP81.1, U32.16
ESP32_GPIO13_TCK6: J107.4, JP95.1, U38.16
ESP32_GPIO13_TCK7: J123.4, JP109.1, U44.16
ESP32_GPIO13_TCK8: J139.4, JP123.1, U50.16
ESP32_GPIO13_TCK9: J155.4, JP137.1, U56.16
ESP32_GPIO13_TCK10: J171.4, JP151.1, U62.16
ESP32_GPIO13_TCK11: J187.4, JP165.1, U68.16
ESP32_GPIO14: J33.10A, J33.10B, J39.10, U14.11
ESP32_GPIO14_HDR: J7.5, J8.5, JP14.2
ESP32_GPIO14_HDR1: J19.5, J26.5, JP26.2
ESP32_GPIO14_HDR2: J35.5, J42.5, JP40.2
ESP32_GPIO14_HDR3: J51.5, J58.5, JP54.2
ESP32_GPIO14_HDR4: J67.5, J74.5, JP68.2
ESP32_GPIO14_HDR5: J83.5, J90.5, JP82.2
ESP32_GPIO14_HDR6: J99.5, J106.5, JP96.2
ESP32_GPIO14_HDR7: J115.5, J122.5, JP110.2
ESP32_GPIO14_HDR8: J131.5, J138.5, JP124.2
ESP32_GPIO14_HDR9: J147.5, J154.5, JP138.2
ESP32_GPIO14_HDR10: J163.5, J170.5, JP152.2
ESP32_GPIO14_HDR11: J179.5, J186.5, JP166.2
ESP32_GPIO14_TMS: J4.2, JP14.1, U1.13
ESP32_GPIO14_TMS1: J27.2, JP26.1, U8.13
ESP32_GPIO14_TMS2: J43.2, JP40.1, U14.13
ESP32_GPIO14_TMS3: J59.2, JP54.1, U20.13
ESP32_GPIO14_TMS4: J75.2, JP68.1, U26.13
ESP32_GPIO14_TMS5: J91.2, JP82.1, U32.13
ESP32_GPIO14_TMS6: J107.2, JP96.1, U38.13
ESP32_GPIO14_TMS7: J123.2, JP110.1, U44.13
ESP32_GPIO14_TMS8: J139.2, JP124.1, U50.13
ESP32_GPIO14_TMS9: J155.2, JP138.1, U56.13
ESP32_GPIO14_TMS10: J171.2, JP152.1, U62.13
ESP32_GPIO14_TMS11: J187.2, JP166.1, U68.13
ESP32_GPIO15: J33.9A, J33.9B, J39.9, U14.12
ESP32_GPIO15_TDO: J4.6, U1.23
ESP32_GPIO15_TDO1: J27.6, U8.23
ESP32_GPIO15_TDO2: J43.6, U14.23
ESP32_GPIO15_TDO3: J59.6, U20.23
ESP32_GPIO15_TDO4: J75.6, U26.23
ESP32_GPIO15_TDO5: J91.6, U32.23
ESP32_GPIO15_TDO6: J107.6, U38.23
ESP32_GPIO15_TDO7: J123.6, U44.23
ESP32_GPIO15_TDO8: J139.6, U50.23
ESP32_GPIO15_TDO9: J155.6, U56.23
ESP32_GPIO15_TDO10: J171.6, U62.23
ESP32_GPIO15_TDO11: J187.6, U68.23
ESP32_GPIO16: J7.6, J8.6, U1.27
ESP32_GPIO17: J7.7, J8.7, U1.28
ESP32_GPIO18: J35.6, J42.6, U14.27
ESP32_GPIO18_SCK: D6.A, J5.5, J6.5A, J6.5B, J15.5, U1.30
ESP32_GPIO18_SCK1: D9.A, J17.5A, J17.5B, J23.5, J29.5, U8.30
ESP32_GPIO18_SCK2: D15.A, J33.5A, J33.5B, J39.5, J45.5, U14.30
ESP32_GPIO18_SCK3: D21.A, J49.5A, J49.5B, J55.5, J61.5, U20.30
ESP32_GPIO18_SCK4: D27.A, J65.5A, J65.5B, J71.5, J77.5, U26.30
ESP32_GPIO18_SCK5: D33.A, J81.5A, J81.5B, J87.5, J93.5, U32.30
ESP32_GPIO18_SCK6: D39.A, J97.5A, J97.5B, J103.5, J109.5, U38.30
ESP32_GPIO18_SCK7: D45.A, J113.5A, J113.5B, J119.5, J125.5, U44.30
ESP32_GPIO18_SCK8: D51.A, J129.5A, J129.5B, J135.5, J141.5, U50.30
ESP32_GPIO18_SCK9: D57.A, J145.5A, J145.5B, J151.5, J157.5, U56.30
ESP32_GPIO18_SCK10: D63.A, J161.5A, J161.5B, J167.5, J173.5, U62.30
ESP32_GPIO18_SCK11: D69.A, J177.5A, J177.5B, J183.5, J189.5, U68.30
ESP32_GPIO19_POCI: J5.6, J6.6A, J6.6B, J15.7, U1.31
ESP32_GPIO19_POCI1: J17.6A, J17.6B, J23.6, J29.7, U8.31
ESP32_GPIO19_POCI2: J33.6A, J33.6B, J39.6, J45.7, U14.31
ESP32_GPIO19_POCI3: J49.6A, J49.6B, J55.6, J61.7, U20.31
ESP32_GPIO19_POCI4: J65.6A, J65.6B, J71.6, J77.7, U26.31
ESP32_GPIO19_POCI5: J81.6A, J81.6B, J87.6, J93.7, U32.31
ESP32_GPIO19_POCI6: J97.6A, J97.6B, J103.6, J109.7, U38.31
ESP32_GPIO19_POCI7: J113.6A, J113.6B, J119.6, J125.7, U44.31
ESP32_GPIO19_POCI8: J129.6A, J129.6B, J135.6, J141.7, U50.31
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
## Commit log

2021-12-17 Added documents folder.
2021-12-21 Added initial schematic version.
2021-12-21 Added missing Vin symbol.
2021-12-21 Changed pin name from /SS to /CS
2021-12-22 Preliminary routed board, no labels yet.
2021-12-23 Added board labels.
2021-12-27 Added ordering instructions; added production files.
2022-01-03 Changed board per Nathan's recommendations; added production files.
    - Changed SPI pins nomenclatures.
    - Fixed silkscreens.
    - Replaced SD card socket with an updated one.
2022-01-07 Moved SD card connector; updated RST/RESET flags.
2022-01-07 Added version number to filename; updated production files.
2022-01-10 Update README.md
    Initial pass with minimal info
2022-01-11 Added Test Point per Eric Orosel request.
2022-01-12 Fixed trace on bottom side, regenerated panel file.
2022-01-12 Moved BOM file; updated production files.
2022-01-12 Delete hardware/production directory
    Duplicated
2022-01-13 Changed labels as suggested by Chris; updated production files.
2022-01-13 Updated silkscreen.
2022-01-13 Updated to reflect board name.
2022-01-13 Renamed repo/filename to match board name.
2022-01-17 Implemented changes suggested by Pete Lewis.
2022-01-17 Fixed silkscreen and via interference on bottom layer;
2022-01-18 Updated design per Engineering checklist.
2022-01-19 Updated design per Engineering recommendation.
2022-01-31 Flipped Q3, added 100R resistor to Q3's gate and changed panel to 2x2 boards
2022-01-31 Updated BOM
2022-01-31 Updated ordering instructions solder mask color.
2022-03-09 Increase resistors on perfect diodes to reduce quiescent current
2022-05-02 Update cosmetic components and silk
    Change power LED to red
    Change charge LED to yellow
    Change green/yellow LED resistors to 1k
    Change red LED resistor to 2.2k
    Update some top pin silk labels to include pin numbers
    Fix RX silk to be "RX-0" instead of "RX-1"
2022-05-02 Adjust LED jumper
    New position allows better label placement
2022-05-04 Improve GND continuity
    Add several GND vias
    Adjust some traces to allow GND to pour through
2022-05-04 Add "revised by" and change version number
2022-05-04 Change PTC Fuse
    Reduce current rating of PTC
    Move PTC to 5V_MEAS to protect all power inputs rather than just USB
2022-05-04 Add addressable status LED
2022-05-06 Design review updates
    Rename files to remove "v01"
    Update libraries
    Adjust traces under SD card for keepout region
    Change ESP32 footprint from narrow to standard
    Change USB-C connector to 4-layer version
    Add USB shield jumper
2022-05-09 More design review updates
    Add center positive silk marker to barrel jack
    Fix air wire errors in ULP by connecting with traces
    Add SD card detection with NO jumper to GPIO16
2022-05-10 Add NC jumper for each LED
    Also fix barrel jack voltage silk
2022-05-10 Checklist update
    Approve DRC errors on jumpers
    Add space between traces on layer 2
2022-05-11 Design review updates
    Change IO2 to GPIO2 in top silk
    Remove via restrict regions
    Remove test point silk
2022-05-11 Add production files for v02
2022-05-26 Fix A4 and A5 bottom silk labels
2022-05-31 Update version number to v10
2022-05-31 Design review updates
    Add decoupling cap for WS2812
    Move SparkFun logo in top silk
    Add GND via for 3V regulator
    Change I2C label to use superscript 2
    Remove extraneous lines in schematic
    Add warnings about ESP32 boot pins and ADC2/WiFi to schematic
2022-06-01 Design Review Updates
    Change "Revised by" to vector font in tDocu
    Rename jumpers based on their functions
    Add GND trace between GPIO 16/17 in layer 3
2022-06-01 Design review updates
    Clean up SHLD jumper in schematic
    Clean up boot mode table
    Doot
    Move C8 closer to CH340
    Fix natural bridges
    Improve GND continuity
2022-06-02 Pre-production updates
    Update regulator current in schematic
    Change "LED DO" silk label to "NC/LED DO"
2022-06-02 Add production files
2022-06-02 Update panel with fiducials on top/bottom
2022-06-02 Moved panel fiducial and generated gerbers
2022-06-02 Remove old gerber zip
2022-06-02 Fix PROD_ID of new regulator
    Didn't update when it was replaced for some reason
2023-02-09 Updating datasheets per espressif
